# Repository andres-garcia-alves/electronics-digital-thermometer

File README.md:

# Digital Thermometer

Arduino code for a digital thermometer (temperature, humidity and heat index) with auto-OFF functionality.

&nbsp;

This project use the following electronic components:
- 1 x Arduino UNO / Nano v3
- 1 x DHT11 temperature/humidity sensor
- 1 x Display 5461AS, 7 segment, 4 digit, common anode
- 8 x 1k ohm resistors
- 1 x 10k ohm resistor
- 1 x Transistor BC547 NPN
- 1 x Electrolitic capacitor 470uF 10v
- 1 x Push-button
- 1 x Batery 9v

The circuit:
- Pressing the push-button charges the capacitor and puts the transistor in conducting state.
- After the button is released, the capacitor continues to power the base of the transistor for around 20 seconds.
- The current through the transistor powers the Arduino (and rest of the thermometer).
- Arduino constrols the temperature+humidity measurement and the multiplexing process for the 4 digit display.

Notes:
- This thermometer automatically turns off approximately 20 seconds after activation.
- To increase this time, change the capacitor to one of higher capacitance.
- Edit `Definitions.h` to adjust configured display pins to your own display model.

&nbsp;

### Screenshots

| Schematics Diagram                              | PCB Layout                                      |
|-------------------------------------------------|-------------------------------------------------|
|       |              |

| PCB 3D Render                                   | PCB 3D Render                                   |
|-------------------------------------------------|-------------------------------------------------|
|           |           |

| Prototype                                       | Building                                        |
|-------------------------------------------------|-------------------------------------------------|
|               |                |

| Building                                        | Building                                        |
|-------------------------------------------------|-------------------------------------------------|
|                |                |

| Box Shaping                                     | Box Shaping                                     |
|-------------------------------------------------|-------------------------------------------------|
|             |             |

| Project Final                                   | Project Final (YouTube video)                   |
|-------------------------------------------------|-------------------------------------------------|
|           |  |

See 'Rescources' sub-folder for more pictures & videos of the project.

&nbsp;

### Version History

v1.0 (2022.12.08) - Initial release.  
v1.1 (2022.12.10) - Re-arrange LEDs pin-out to simplefy PCB.  
v1.2 (2022.12.11) - Using masked bits to improve character display.  
v1.3 (2023.03.28) - Use of headers for better readability.  
v1.4 (2023.04.08) - Hardware re-desing.  
v1.5 (2025.12.20) - Update project structure.  
v1.6 (2025.12.26) - Adding KiCAD 9 schematics and PCB diagrams.  
v1.7 (2026.02.01) - Minor PCB improvements.  

&nbsp;

This source code is licensed under GPL v3.0  
Please send me your feedback about this project: andres.garcia.alves@gmail.com

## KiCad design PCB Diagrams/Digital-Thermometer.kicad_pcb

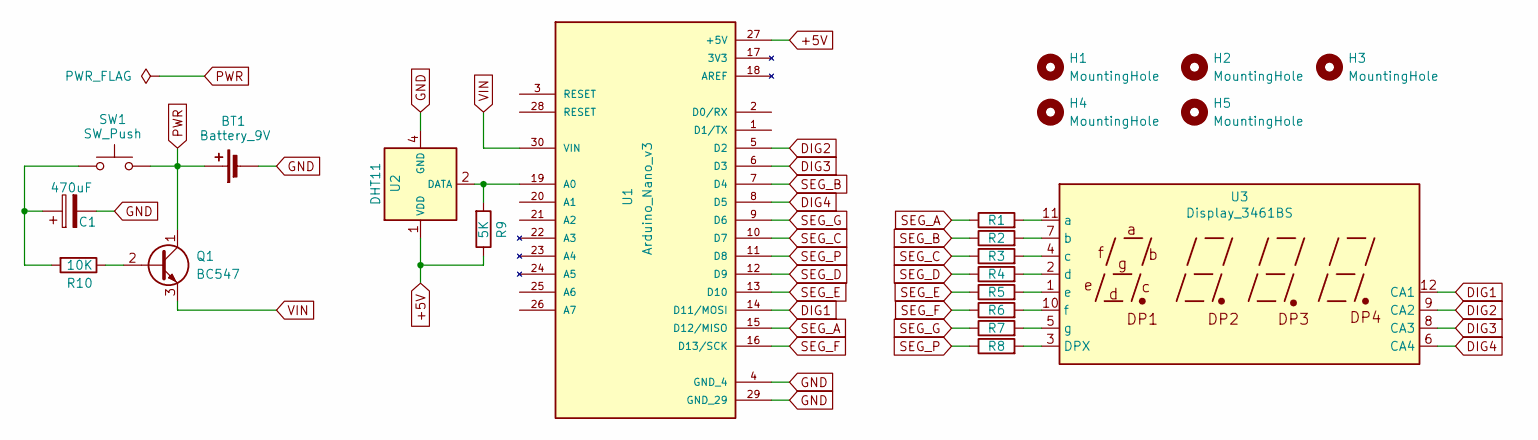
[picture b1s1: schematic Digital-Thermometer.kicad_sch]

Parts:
BT1: Battery_9V; BatteryHolder_Eagle_12BH611-GR
C1: 470uF; C_Radial_D8.0mm_H11.5mm_P3.50mm
H1, H2, H3, H4, H5: MountingHole; MountingHole_2mm
Q1: BC547; TO-92
R1, R2, R3, R4, R5, R6, R7, R8: 1K; R_Axial_DIN0204_L3.6mm_D1.6mm_P2.54mm_Vertical
R9: 5K; R_Axial_DIN0204_L3.6mm_D1.6mm_P2.54mm_Vertical
R10: 10K; R_Axial_DIN0204_L3.6mm_D1.6mm_P2.54mm_Vertical
SW1: SW_Push; SW_PUSH_6mm_H8mm
U1: Arduino_Nano_v3
U2: DHT11; Aosong_DHT11_5.5x12.0_P2.54mm
U3: Display_3461BS; CA56-12EWA

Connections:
+5V: R9.1, U1.27 (+5V), U2.1 (VDD)
DIG1: U1.14 (D11/MOSI), U3.12 (CA1)
DIG2: U1.5 (D2), U3.9 (CA2)
DIG3: U1.6 (D3), U3.8 (CA3)
DIG4: U1.8 (D5), U3.6 (CA4)
GND: BT1.2 (-), C1.2, U1.4 (GND_4), U1.29 (GND_29), U2.4 (GND)
unnamed: C1.1, R10.2, SW1.1
unnamed: Q1.2 (B), R10.1
unnamed: R9.2, U1.19 (A0), U2.2 (DATA)
unnamed: R8.2, U3.3 (DPX)
unnamed: R1.2, U3.11 (a)
unnamed: R2.2, U3.7 (b)
unnamed: R3.2, U3.4 (c)
unnamed: R4.2, U3.2 (d)
unnamed: R5.2, U3.1 (e)
unnamed: R6.2, U3.10 (f)
unnamed: R7.2, U3.5 (g)
PWR: BT1.1 (+), Q1.1 (C), SW1.2
SEG_A: R1.1, U1.15 (D12/MISO)
SEG_B: R2.1, U1.7 (D4)
SEG_C: R3.1, U1.10 (D7)
SEG_D: R4.1, U1.12 (D9)
SEG_E: R5.1, U1.13 (D10)
SEG_F: R6.1, U1.16 (D13/SCK)
SEG_G: R7.1, U1.9 (D6)
SEG_P: R8.1, U1.11 (D8)
VIN: Q1.3 (E), U1.30 (VIN)

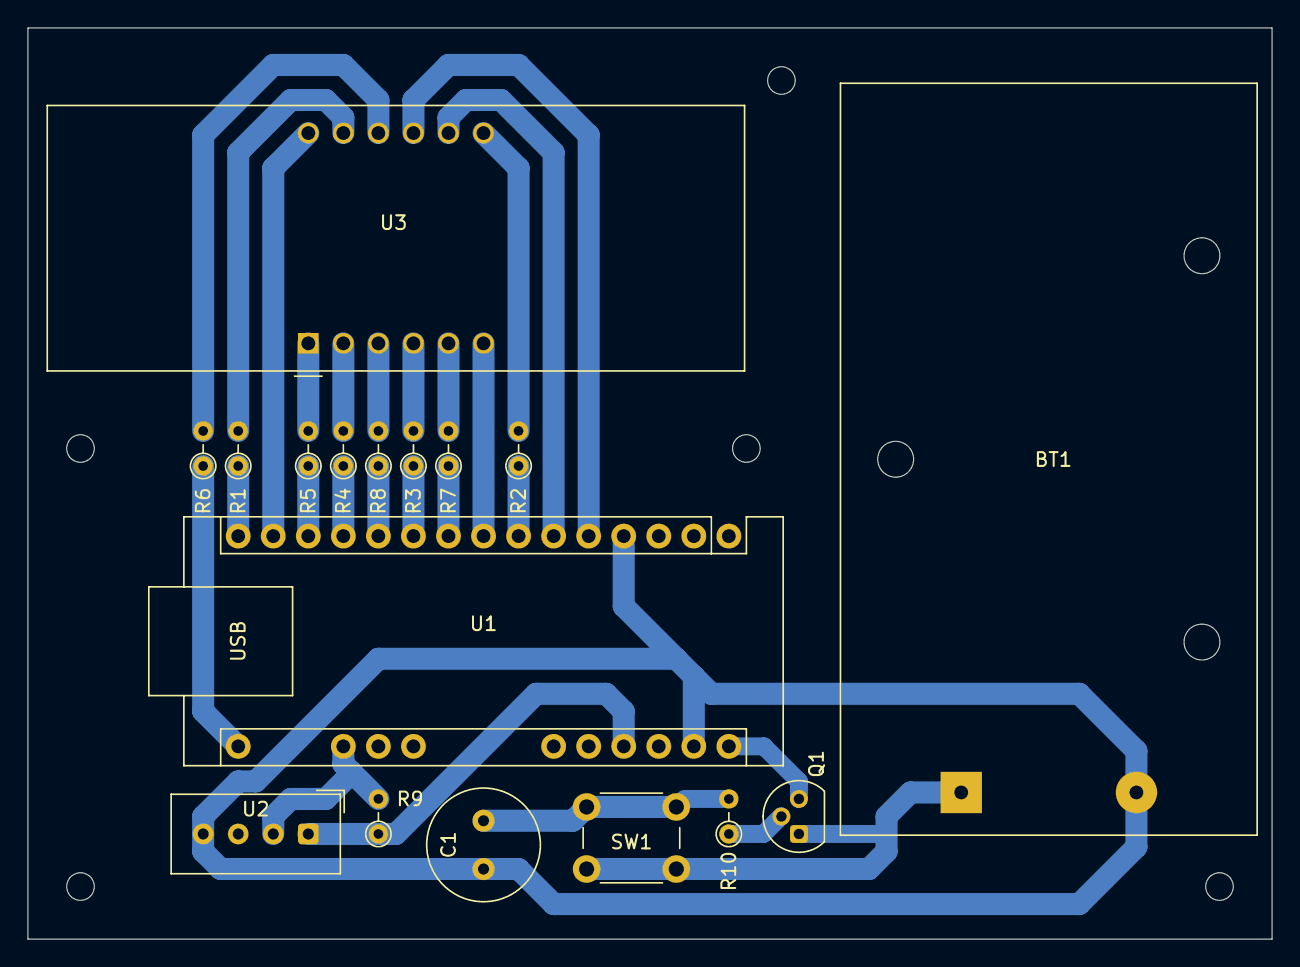
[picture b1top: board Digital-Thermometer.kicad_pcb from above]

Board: 2 copper layers, 90.2 x 66.0 mm, 22 parts (0 on the bottom side), 27 nets.

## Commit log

2023-03-28 adding 'Resources' directory
2023-03-28 updating README.md
2023-03-29 use of headers for better readability
2023-04-02 updating Resources
2023-07-06 update Resources folder
2025-12-20 repo cleaning commit
2025-12-27 Adding KiCAD 9 schematics and PCB diagrams.
2025-12-27 Adding KiCAD 9 schematics and PCB diagrams
2026-02-02 Minor PCB improvements
